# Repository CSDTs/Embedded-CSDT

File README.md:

# Embedded-CSDT
The embedded CSDT projects

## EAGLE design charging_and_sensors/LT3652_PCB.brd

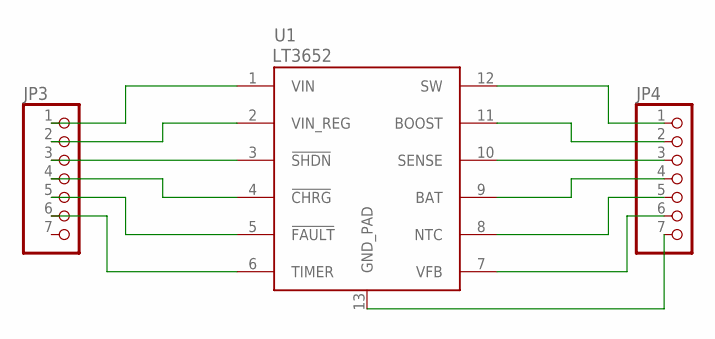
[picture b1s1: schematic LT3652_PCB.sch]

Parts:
JP3, JP4: PINHD-1X7; 1X07
U1: LT3652; MSOP-12_GND

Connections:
unnamed: JP3.1, U1.1 (VIN)
unnamed: JP3.2, U1.2 (VIN_REG)
unnamed: JP3.3, U1.3 (!SHDN)
unnamed: JP3.4, U1.4 (!CHRG)
unnamed: JP3.5, U1.5 (!FAULT)
unnamed: JP3.6, U1.6 (TIMER)
unnamed: JP4.1, U1.12 (SW)
unnamed: JP4.2, U1.11 (BOOST)
unnamed: JP4.3, U1.10 (SENSE)
unnamed: JP4.4, U1.9 (BAT)
unnamed: JP4.5, U1.8 (NTC)
unnamed: JP4.6, U1.7 (VFB)
unnamed: JP4.7, U1.13 (GND_PAD)

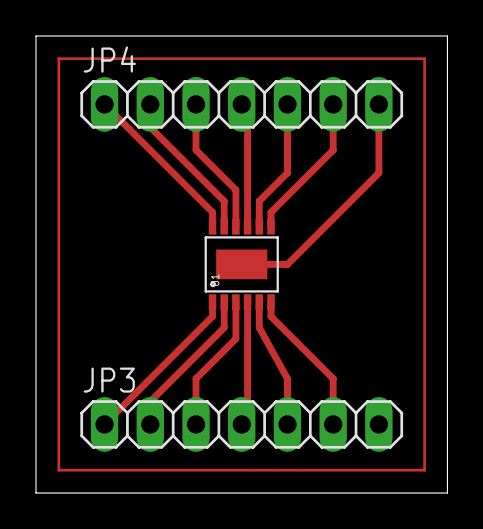
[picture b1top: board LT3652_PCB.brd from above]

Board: 2 copper layers, 22.9 x 25.4 mm, 3 parts (0 on the bottom side), 13 nets.

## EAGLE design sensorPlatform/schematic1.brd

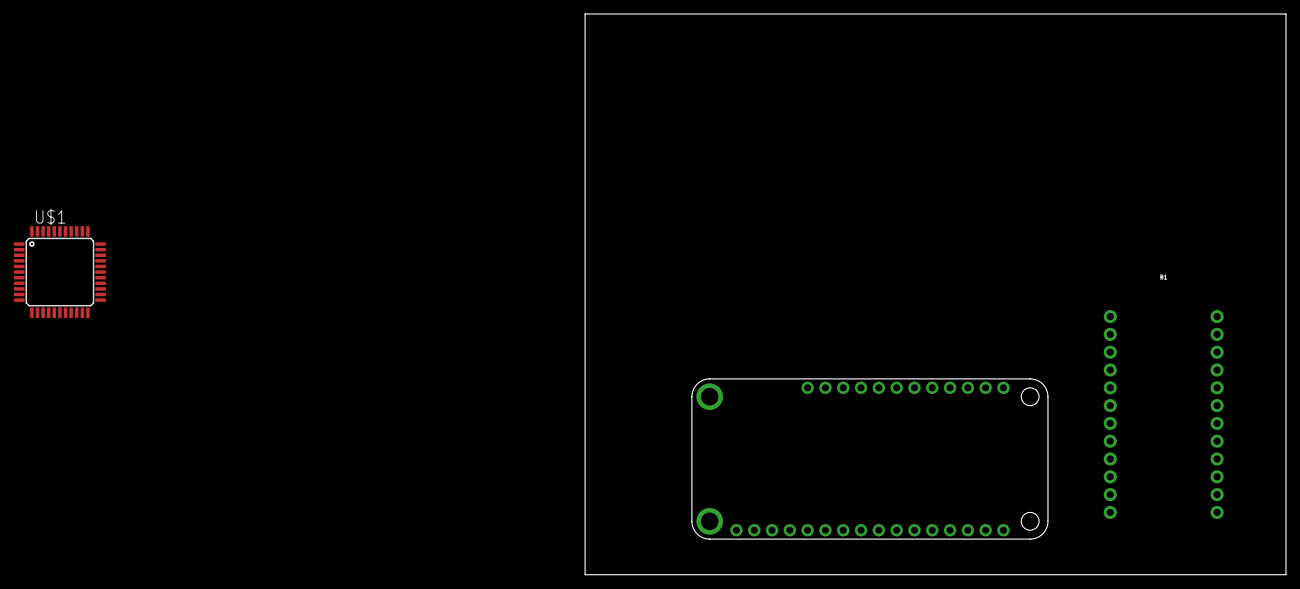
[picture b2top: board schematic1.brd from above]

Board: 2 copper layers, 100.0 x 80.0 mm, 3 parts (0 on the bottom side), 2 nets, no tracks yet.

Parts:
B1: SPARKFUN_PRO_MICRO
MS1: FEATHERWING
U$1: ATMEGA32U4-AU; TQFP44

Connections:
3.3V: MS1.4, U$1.15
GND: B1.3, B1.4, B1.23

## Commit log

2018-01-26 Hardware_needed,Circuit
2018-01-29 draft,hard_ware
2018-01-29 circuit_change
2018-02-02 amplifier_needed
2018-02-05 muscle_detector_circuit
2018-02-06 Add files via upload
    This first iteration uses a Wheatstone bridge with the hair bundle in one leg to obtain an accurate measurement of voltage. Voltage followers built with high input impedance op-amps are used to "isol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
2018-02-07 Add files via upload
    The Previous version of the circuit has a problem when the hair resistance is smaller than the three reference resistors in the bridge, the output voltage goes negative, which is unusable by Adruino 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
2018-02-07 Add files via upload
    Since The conductivity of the hair sample is not likely to change during the experiment, if precision is not a concern, a simpler circuit with a voltage divider can be used to measure the conductivit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
2018-02-07 <This folder contains schematics and circuit designs for the hair strength testing system, and the filr readme will have a more elaborated instructions and introductions.>
2018-02-07 Create Instructions
2018-02-07 Commit 2/7/18 - Jessy Kauffman
    I built a schematic in EAGLE using the required parts given in
    ADAFRUIT as well as Spark-Fun and connected them so that there would be
    voltage going between the parts. The parts used are the ADAFRUIT FoNa,
    Pro Micro, the Featherwing, and voltage sources for the solar panel and
    the two batteries
2018-02-08 Add files via upload
    This first iteration uses a Wheatstone bridge with the hair bundle in one leg to obtain an accurate measurement of voltage. Voltage followers built with high input impedance op-amps are used to "isol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
2018-02-08 The file two_ldrs.sch is the eagle circuit schmetic of making two voltage dividers using two photoresistors. The sensor_reading.ino file is the arduino file of reading voltage drop over LEDs. Althoug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
2018-02-14 modified circuits
2018-02-14 Modified circuits that replaced the two LEDs with resistors
2018-02-15 Moving Jimmy's stuff
2018-02-21 Revert "The file two_ldrs.sch is the eagle circuit schmetic of making two voltage dividers using two photoresistors."
    This reverts commit 4e299daec8d24607c93e16d000a2b2d47be1f488.
2018-03-04 Add files via upload
    Schematics for use with bq24560 or lt3652 solar charger controllers
2018-03-07 Add files via upload
    Charge controllers and sensor schematics
2018-03-07 Add files via upload
    sensor schematic connections to the pro micro
2018-05-16 My test commit
    First day
2018-05-18 Added Salinity Probe Test
2018-05-29 updating the code to have better calibration etc.
2018-05-29 Code for the DS18B20 Temperature Sensor and DFRobot Turbidity Sensor
2018-06-13 schematics of the circuit design(editable version)
2018-06-13 Final circuit schematics (version for read)
2018-06-18 Create yahtzee!
2018-06-18 Add files via upload
    Included are the arduino files for the first bombshell prototype.
2018-06-18 Add files via upload
    Added arduino files for first protoype
2018-06-19 Added initial files for heart rate sensor with arduino and for modulating audio speed.
2018-08-07 Add files via upload
    code for matlab (distribution & fit function) and c++(to insert the fit equation from matlab and output force from voltage)
2018-08-07 Some measuring data to build the system
2018-08-09 Final report for force testing system

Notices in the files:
parts and their libraries:
SparkFun-IC-Power: Licensing: Creative Commons ShareAlike 4.0 International - https://creativecommons.org/licenses/by-sa/4.0
